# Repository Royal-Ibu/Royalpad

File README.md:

# Royalpad
A Custom 9-key Macropad with an EC11 Rotary Encoder, 0.91-inch OLED Display, and Custom KiCad PCB Built for Productivity. Royalpad was made as a submission for [Hackpad V5](https://hackpad.hackclub.com/) through the Stardance challenge.

## Overview
Royalpad is a custom macropad that uses the Seeed Studio XIAO RP2040, QMK firmware, and brings nine mechanical MX switches, a clickable rotary encoder, and a small OLED display. Whether you're coding, CADding, trying to be productive, or doomscrolling optimally, this macropad is the tool for the job.

## Renders

## Features
- 3x3 Matrix Layout: A compact 3 × 3 grid of mechanical switches.
- EC11 Rotary Encoder: Provides rotational input and a push-button click.
- 0.91-inch OLED Display: A small screen for status or other information.
- XIAO RP2040 Controller: A compact microcontroller board for the macropad.
- Custom PCB: Designed in KiCad.
- QMK Firmware: open-source firmware for maximum control
- A cool case with triangle cutouts, because why not?

## Bill of Materials (BOM)

| Component | Quantity | Specifications | Source / Notes |
|---|---:|---|---|
| Seeed XIAO RP2040 | 1 | Unsoldered microcontroller board | [Seeed Studio Documentation](https://wiki.seeedstudio.com/XIAO-RP2040/) |
| 1N4148 Diodes | 9 | Through-hole diodes, one per switch | [Vishay Datasheet](https://www.vishay.com/docs/81857/1n4148.pdf) |
| MX-Style Switches | 9 | Mechanical keyboard switches | [Switch Datasheet](https://cdn.shopify.com/s/files/1/0565/8070/2297/files/SPEC-KS-3Y10B050NW-X1-Yellow_Switch.pdf?v=1675841028) |
| EC11E Rotary Encoder | 1 | Incremental rotary encoder with integrated push button | [Encoder Datasheet](https://mm.digikey.com/Volume0/opasdata/d220001/medias/docus/6727/alps_alps-s-a0008379064-1-1733314-1-13.pdf) |
| 0.91-inch OLED Display | 1 | Compact display module | Provided by Hack Club |
| White Blank DSA Keycaps | 9 | Blank DSA-profile keycaps compatible with the selected switches | White, unlabelled keycaps - Provided by Hack Club |
| M3 × 16 mm Screws | 4 | Enclosure mounting fasteners | Provided by Hack Club |
| Custom PCB | 1 | Custom-designed Royalpad circuit board | Designed in KiCad |
| 3D-Printed Top Case | 1 | Upper enclosure for the macropad | Designed in SolidWorks |
| 3D-Printed Bottom Case | 1 | Lower enclosure housing the PCB and electronics | Designed in SolidWorks |
| Rotary Encoder Knob | 1 | Knob compatible with the EC11E encoder shaft | Provided by Hack Club |

## Firmware overview
RoyalPad uses QMK firmware to turn its nine-key macropad into five different shortcut layers. The active layer determines what each key and the rotary encoder do. The OLED displays the active mode and provides an on-screen menu for switching between modes.
Main firmware features
- Five modes: Main, Productivity, SOLIDWORKS, Coding and KiCad.
- OLED display: Shows the active mode and the mode-selection menu.
- Rotary encoder mode selector: Hold the encoder's push switch for five seconds to open the menu, rotate to move through the options, then press the encoder to select a mode.
- Mode-specific encoder controls: The encoder changes behaviour depending on the selected mode.
- Custom shortcuts: Key functions target common actions in everyday computer use, productivity applications, CAD, coding and PCB design.
Mode-specific key functions
The table below uses a left-to-right, top-to-bottom key order, from K1 to K9.

### Layer 0: Main

| Key | Function |
|---|---|
| K1 | Copy |
| K2 | Paste |
| K3 | Undo |
| K4 | Cut |
| K5 | Save |
| K6 | Select All |
| K7 | Previous Track |
| K8 | Play/Pause |
| K9 | Next Track |

**Rotary Encoder:** Turn to control system volume. Short press to mute or unmute.

### Layer 1: Productivity

| Key | Function |
|---|---|
| K1 | Open Notion |
| K2 | Open ChatGPT |
| K3 | Open Gmail |
| K4 | Screenshot |
| K5 | Open Study Focus Pomodoro |
| K6 | Clipboard |
| K7 | Calendar |
| K8 | New Tab |
| K9 | Task View |

**Rotary Encoder:** Page Up / Page Down navigation.

### Layer 2: SOLIDWORKS
**Note:** The first eight commands use custom `Ctrl + Alt + 1` through `Ctrl + Alt + 8` shortcuts configured in SOLIDWORKS. Zoom to Fit uses the standard `F` shortcut.

| Key | Function |
|---|---|
| K1 | Start Sketch |
| K2 | Smart Dimension |
| K3 | Line |
| K4 | Corner Rectangle |
| K5 | Sketch Fillet |
| K6 | Trim Entities |
| K7 | Linear Sketch Pattern |
| K8 | Exit Sketch |
| K9 | Zoom to Fit |

**Rotary Encoder:** Mouse-wheel viewport zoom.

### Layer 3: Coding

| Key | Function |
|---|---|
| K1 | Open GitHub |
| K2 | Open Visual Studio Code |
| K3 | Open Terminal |
| K4 | Copy |
| K5 | Paste |
| K6 | Cut |
| K7 | Undo |
| K8 | Redo |
| K9 | Save |

**Rotary Encoder:** Page Up / Page Down navigation.

### Layer 4: KiCad

| Key | Function |
|---|---|
| K1 | Add Footprint |
| K2 | Route Tracks |
| K3 | Properties |
| K4 | Move |
| K5 | Rotate |
| K6 | Flip Footprint |
| K7 | Save |
| K8 | Refill Zones |
| K9 | Open 3D Viewer |

**Rotary Encoder:** Switch between the `B.Cu` and `F.Cu` copper layers.

## Additional Notes
- Some SOLIDWORKS shortcuts require separate configuration within SOLIDWORKS.
- Application-launch keys depend on the configured URLs or applications.
- KiCad shortcuts may vary depending on the active editor and shortcut configuration.
- Firmware updates require compiling and flashing a new .uf2 file.

A huge thank you to **Stardance and Hack Club** for providing such an awesome opportunity to design, build, and share a custom hardware project through the Hackpad Challenge!

Royalpad was my first time designing a custom PCB and building a custom hardware project. Throughout the process, I learned how to design and lay out a PCB using KiCad, including working with components such as MX-style switches, diodes, and a rotary encoder. I also used SOLIDWORKS to design a custom two-piece enclosure that fits the PCB and other components nicely. Beyond the hardware itself, this project gave me the opportunity to explore firmware and learn more about how software interacts with custom electronics. It was a great introduction to QMK firmware, as it was definitely a challenge to compile and code everything my Royalpad needed, especially for the various mode layers. I took inspiration from ReuTheCoder's [Stratum](https://github.com/ReuTheCoder/stratum-macropad) in terms of how it utilizes different layers where each key performs a different function.

Most importantly, Royalpad gave me the confidence to take on a project that was completely new to me, work through unfamiliar tools and challenges, and develop skills that I can carry into future electronics, CAD, and engineering projects. I'm really grateful to Hack Club and Stardance for making this experience possible!

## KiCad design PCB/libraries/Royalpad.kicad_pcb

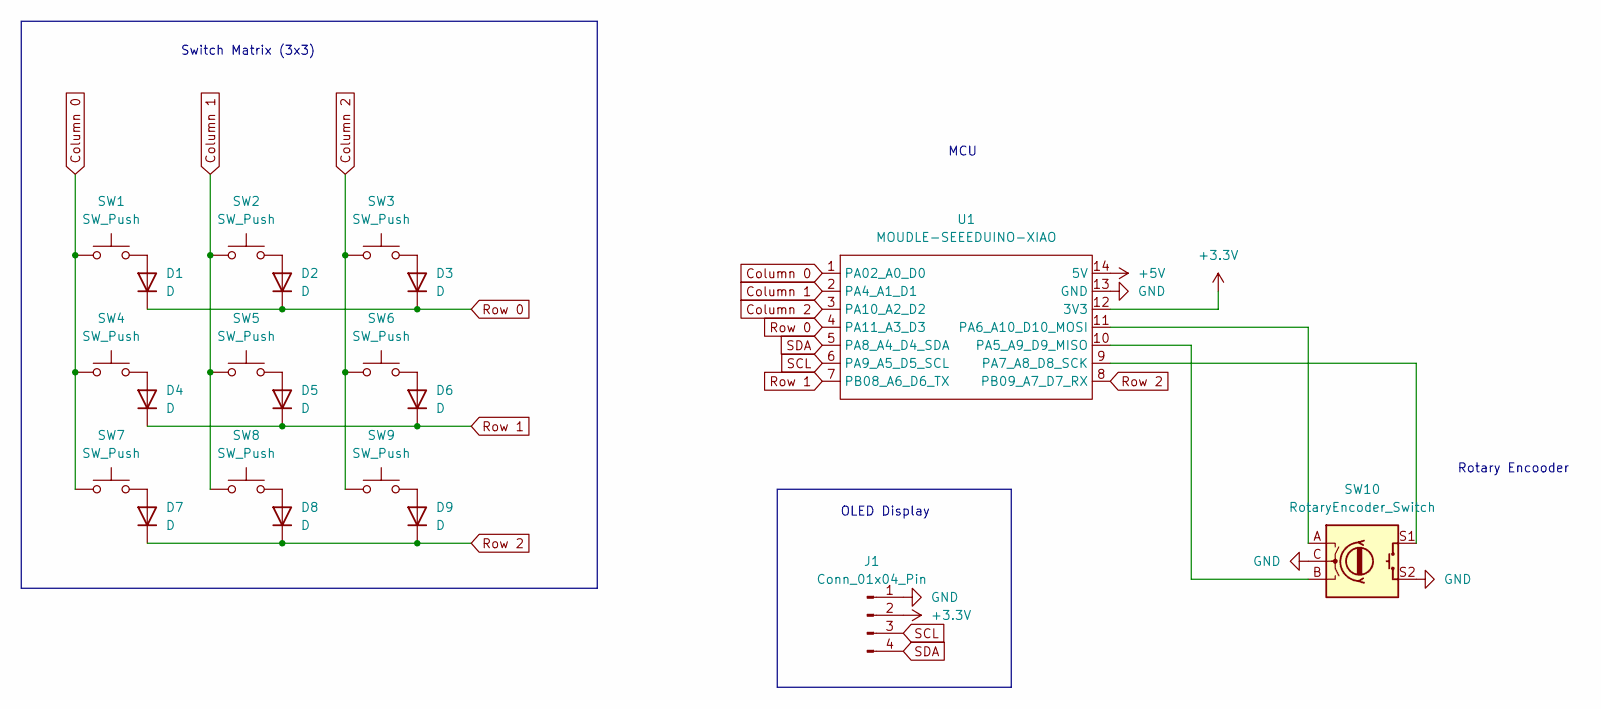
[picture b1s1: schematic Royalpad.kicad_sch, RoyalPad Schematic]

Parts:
D1, D2, D3, D4, D5, D6, D7, D8, D9: D; D_DO-35_SOD27_P7.62mm_Horizontal
J1: Conn_01x04_Pin; SSD1306-0.91-OLED-4pin-128x32
SW1, SW2, SW3, SW4, SW5, SW6, SW7, SW8, SW9: SW_Push; SW_Cherry_MX_1.00u_PCB
SW10: RotaryEncoder_Switch; RotaryEncoder_Alps_EC11E-Switch_Vertical_H20mm
U1: MOUDLE-SEEEDUINO-XIAO; XIAO-Generic-Hybrid-14P-2.54-21X17.8MM

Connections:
+3.3V: J1.2, U1.12 (3V3)
+5V: U1.14 (5V)
Column 0: SW1.1, SW4.1, SW7.1, U1.1 (PA02_A0_D0)
Column 1: SW2.1, SW5.1, SW8.1, U1.2 (PA4_A1_D1)
Column 2: SW3.1, SW6.1, SW9.1, U1.3 (PA10_A2_D2)
GND: J1.1, SW10.C, SW10.S2, U1.13 (GND)
unnamed: D1.2 (A), SW1.2
unnamed: D2.2 (A), SW2.2
unnamed: D3.2 (A), SW3.2
unnamed: D4.2 (A), SW4.2
unnamed: D5.2 (A), SW5.2
unnamed: D6.2 (A), SW6.2
unnamed: D7.2 (A), SW7.2
unnamed: D8.2 (A), SW8.2
unnamed: D9.2 (A), SW9.2
unnamed: SW10.B, U1.10 (PA5_A9_D9_MISO)
unnamed: SW10.A, U1.11 (PA6_A10_D10_MOSI)
unnamed: SW10.S1, U1.9 (PA7_A8_D8_SCK)
Row 0: D1.1 (K), D2.1 (K), D3.1 (K), U1.4 (PA11_A3_D3)
Row 1: D4.1 (K), D5.1 (K), D6.1 (K), U1.7 (PB08_A6_D6_TX)
Row 2: D7.1 (K), D8.1 (K), D9.1 (K), U1.8 (PB09_A7_D7_RX)
SCL: J1.3, U1.6 (PA9_A5_D5_SCL)
SDA: J1.4, U1.5 (PA8_A4_D4_SDA)

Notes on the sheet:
MCU
Switch Matrix (3x3)
OLED Display
Rotary Encooder

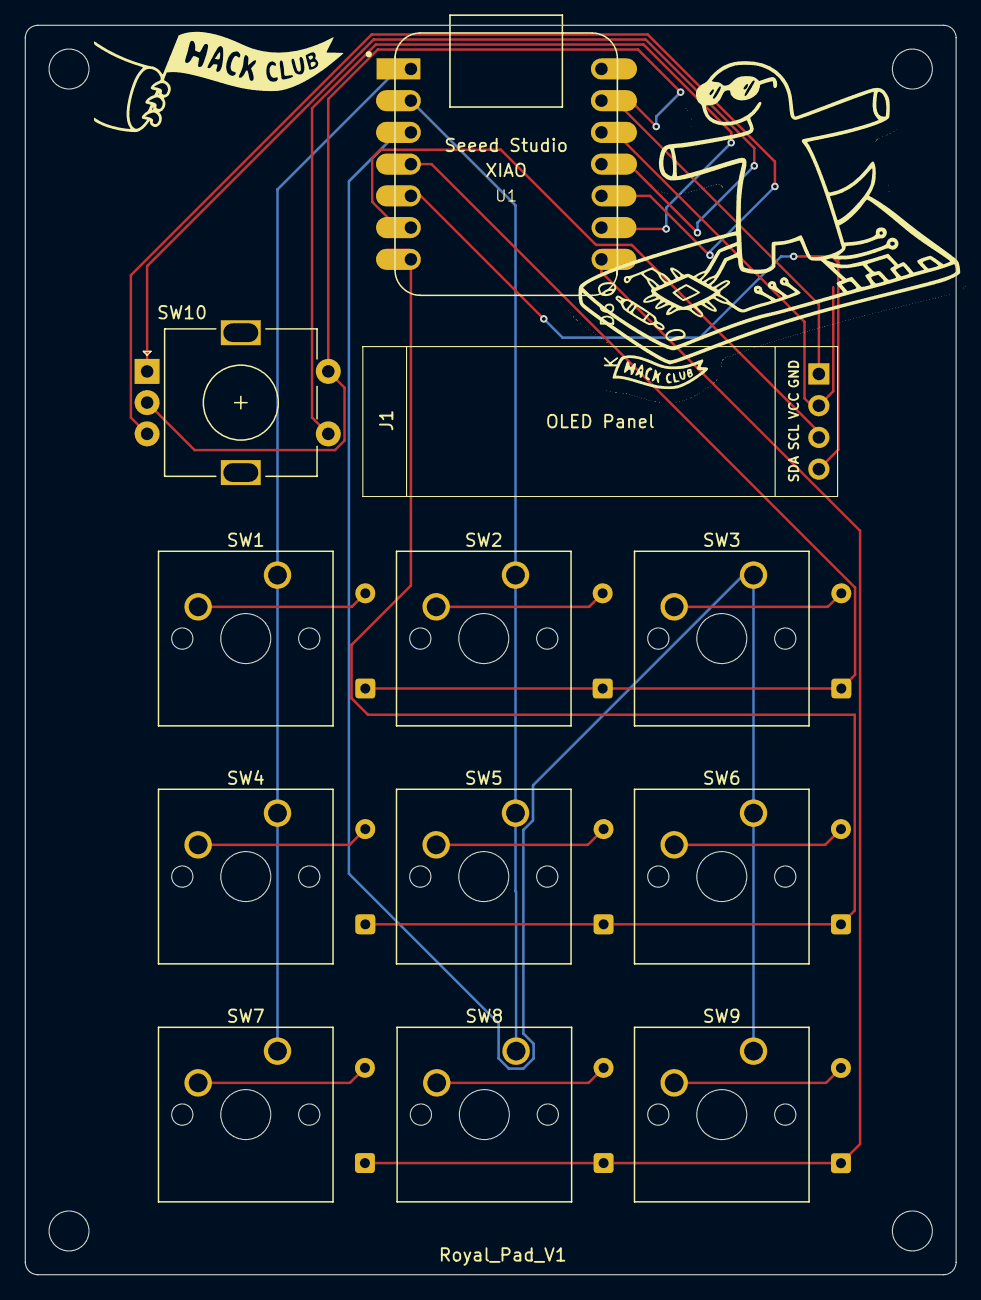
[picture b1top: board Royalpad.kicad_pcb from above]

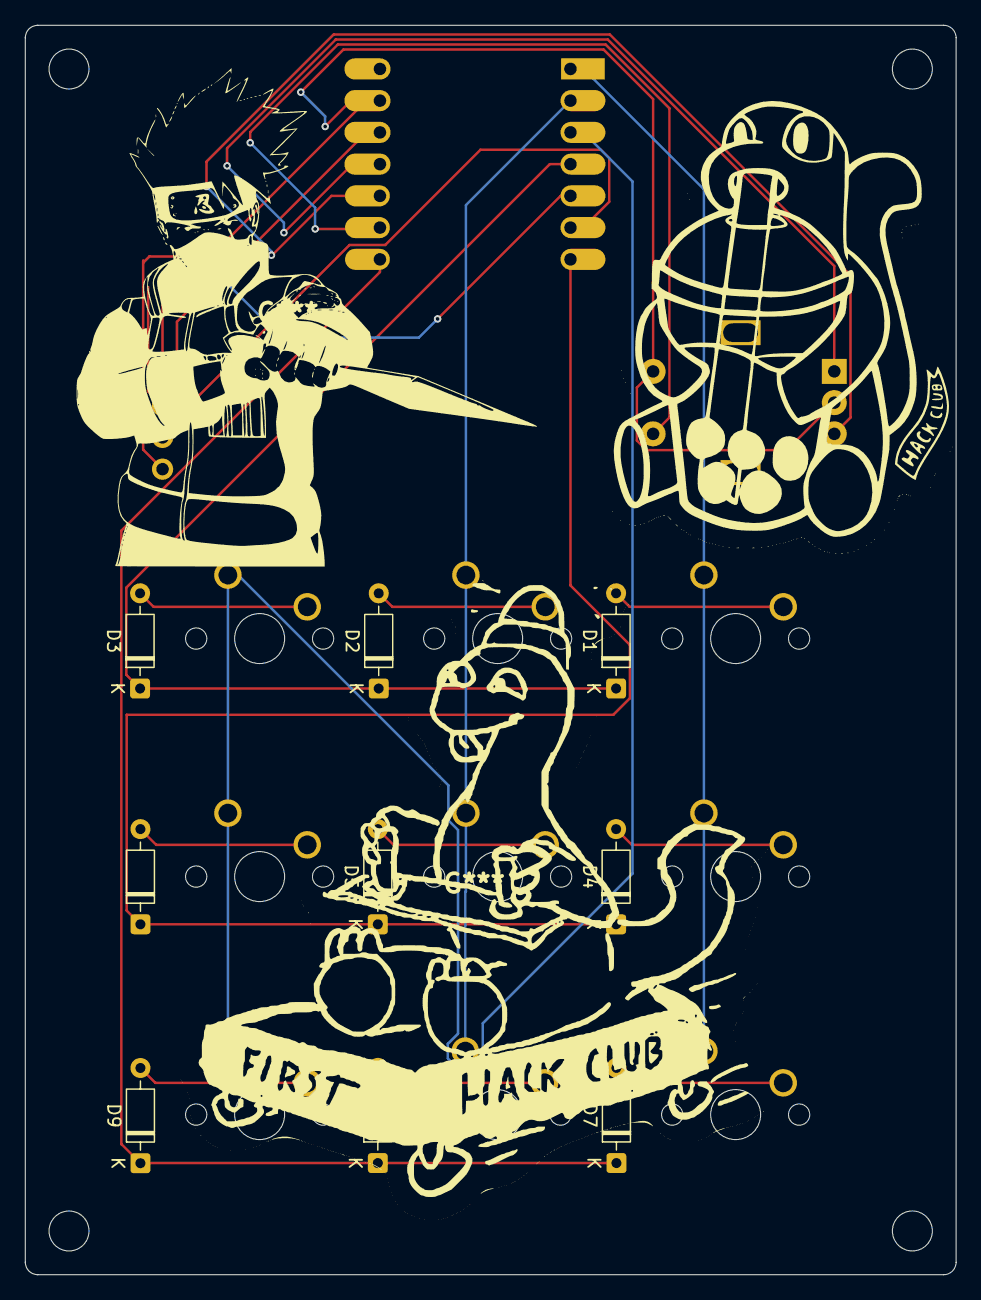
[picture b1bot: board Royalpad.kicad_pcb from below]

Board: 2 copper layers, 74.5 x 100.0 mm, 21 parts (9 on the bottom side), 22 nets.
